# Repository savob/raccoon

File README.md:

# Raccoon

A little raccoon trinket based on an ATtiny and capacitive sensing. The premise is simple, a small circuitboard decorated to be a raccoon on one side has circuitry mounted on the back to illuminate the LED eyes when a touch is detected on the raccoon. Designed to maximize battery life and run of standard coin cells.

My first foray into making PCB art hardwarewise, and both capacitive sensing and really trying to supress power draw with coding.

_All this artwork was drawn by my lovely sister, Dorotea Bajic. Check out their website [dorotea.ca](https://dorotea.ca/), it's far nicer looking than my own._

# Code

The code is pretty simple for the first two revisions given the scope of the projects, and a minor hack was used to get revision 1.0 working. I used the Arduino framework for the first revision but have since moved to using Microchip's own MPLAB to make full use of the chips.

# Hardware

The electrical design of the system is simple, a microcontroller powered directly from a coin cell battery that is connected to a couple LEDs, a capacitance detection pad, and a select few passive components. The challenge with the board for this was the artwork and making it look nice.

Initially an ATtiny85 was selected but later I switched to the tinyAVR 1-series due to dedicated capacitive sensing hardware and reduced power consumption.

# Software Used

KiCad is used to design the hardware, version 9 as of writing.

Arduino IDE 1.8.13 was used to program revision 1.0. MPLAB for revisions 2.0 onwards.

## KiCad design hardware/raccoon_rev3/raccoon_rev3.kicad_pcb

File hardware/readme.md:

# Raccoon Hardware Files

The folders `raccoon_revX` are the actual KiCad projects, `raccoon-art` is the collection of footprints for the artwork derived from the images in the [media](../media/) folder.

# Revision 1.0

These design files are the lightly adjusted version of the original raccoon hardware, to address the hardware bugs related to the programming interface.

# Revision 2.0

A continuation of the work done for the files shared as "Revision 1". Changes from the previous revision:

- Complete removal of the ATtiny85 in favour of the ATtiny1617 _which is definitely overkill for this task but what I had on hand._
- Moved to using a TagConnect programming header to simplify programming. _This does slightly affect the art on the front._
- Added a jumper to cut for current measurement

# Revision 3.0

Tweaking the design of revision 2.0. Changes from the previous revision:

- Changed the main microcontroller to a 1616 since we don't need many GPIO, but I want flash space to try different eye effects, maybe even changing with each touch
- Removed unnecessary passives; the sense resistor, VREF capacitor, secondary decoupling capacitor (100n)
- Split the LED lines for individual eye control, via PWM
- Moved the programming pads to be closer to the edge so some alignment pins align to the PCB outline instead of needing holes in the PCB
- Moved the LED current limiting resistors to be closer to the microcontroller and out of the path of the coin cell
- Added a keepout zone for pour near the current measurement jumper to avoid cutting and then shorting VCC to GND

# Software Used

KiCad version 9 was used for all project files.

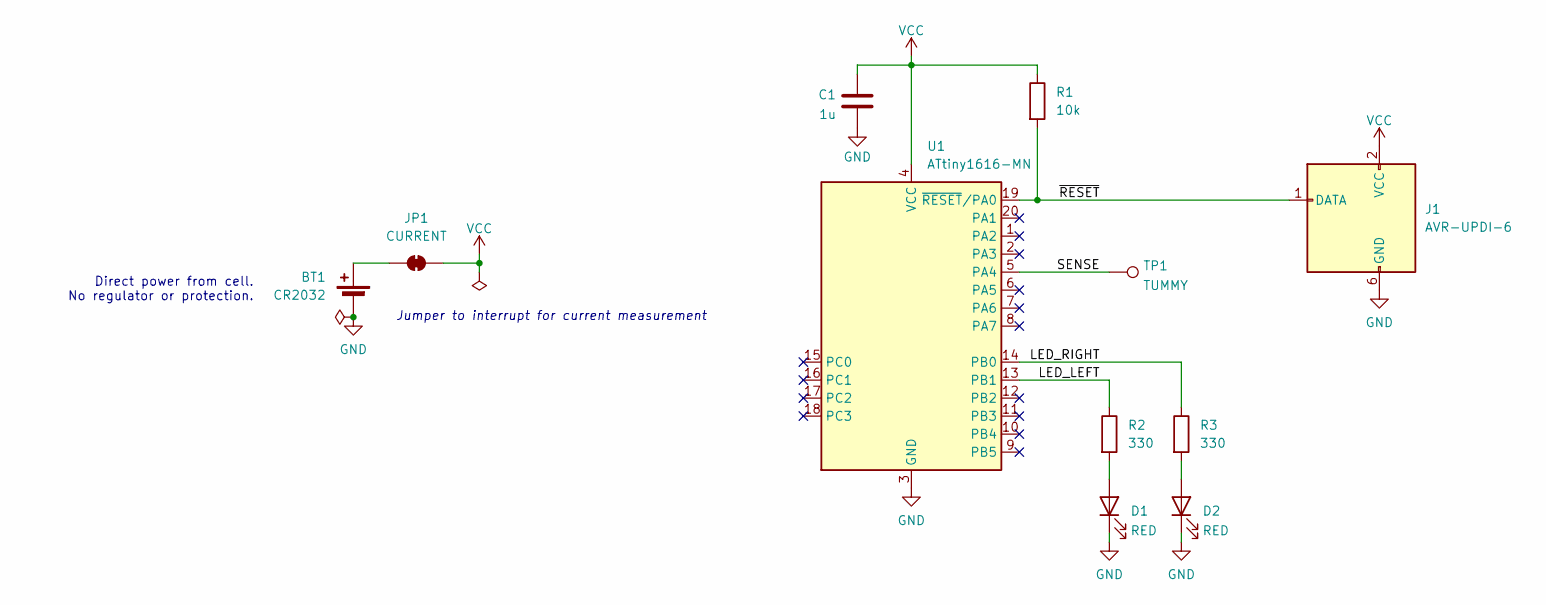
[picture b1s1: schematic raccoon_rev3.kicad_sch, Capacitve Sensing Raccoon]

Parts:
BT1: CR2032; BatteryHolder_Multicomp_BC-2001_1x2032; Manufacturer PN MY-2032-05; LCSC C964830
C1: 1u; C_0603_1608Metric; Manufacturer PN CL10A105KB8NNNC; LCSC C15849
D1, D2: RED; D_0805_2012Metric; Manufacturer PN LTST-C170KRKT; LCSC C94868
J1: AVR-UPDI-6; Tag-Connect_TC2030-IDC-NL_2x03_P1.27mm_Vertical
JP1: CURRENT; SolderJumper-2_P1.3mm_Bridged2Bar_Pad1.0x1.5mm
R1: 10k; R_0603_1608Metric; Manufacturer PN 0603WAF1002T5E; LCSC C25804
R2, R3: 330; R_0603_1608Metric; Manufacturer PN 0603WAF3300T5E; LCSC C23138
TP1: TUMMY; tummy
U1: ATtiny1616-MN; VQFN-20-1EP_3x3mm_P0.4mm_EP1.7x1.7mm; Manufacturer PN ATTINY1616-MNR; LCSC C507118

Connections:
/LED_LEFT: R2.1, U1.13 (PB1)
/LED_RIGHT: R3.1, U1.14 (PB0)
/SENSE: TP1.1, U1.5 (PA4)
/~RESET: J1.1 (DATA), R1.2, U1.19 (~RESET/PA0)
GND: BT1.2 (-), C1.2, D1.1 (K), D2.1 (K), J1.6 (GND), U1.3 (GND), U1.21 (GND)
unnamed: BT1.1 (+), JP1.1 (A)
unnamed: D1.2 (A), R2.2
unnamed: D2.2 (A), R3.2
VCC: C1.1, J1.2 (VCC), JP1.2 (B), R1.1, U1.4 (VCC)

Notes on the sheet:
Jumper to interrupt for current measurement
Direct power from cell. No regulator or protection.

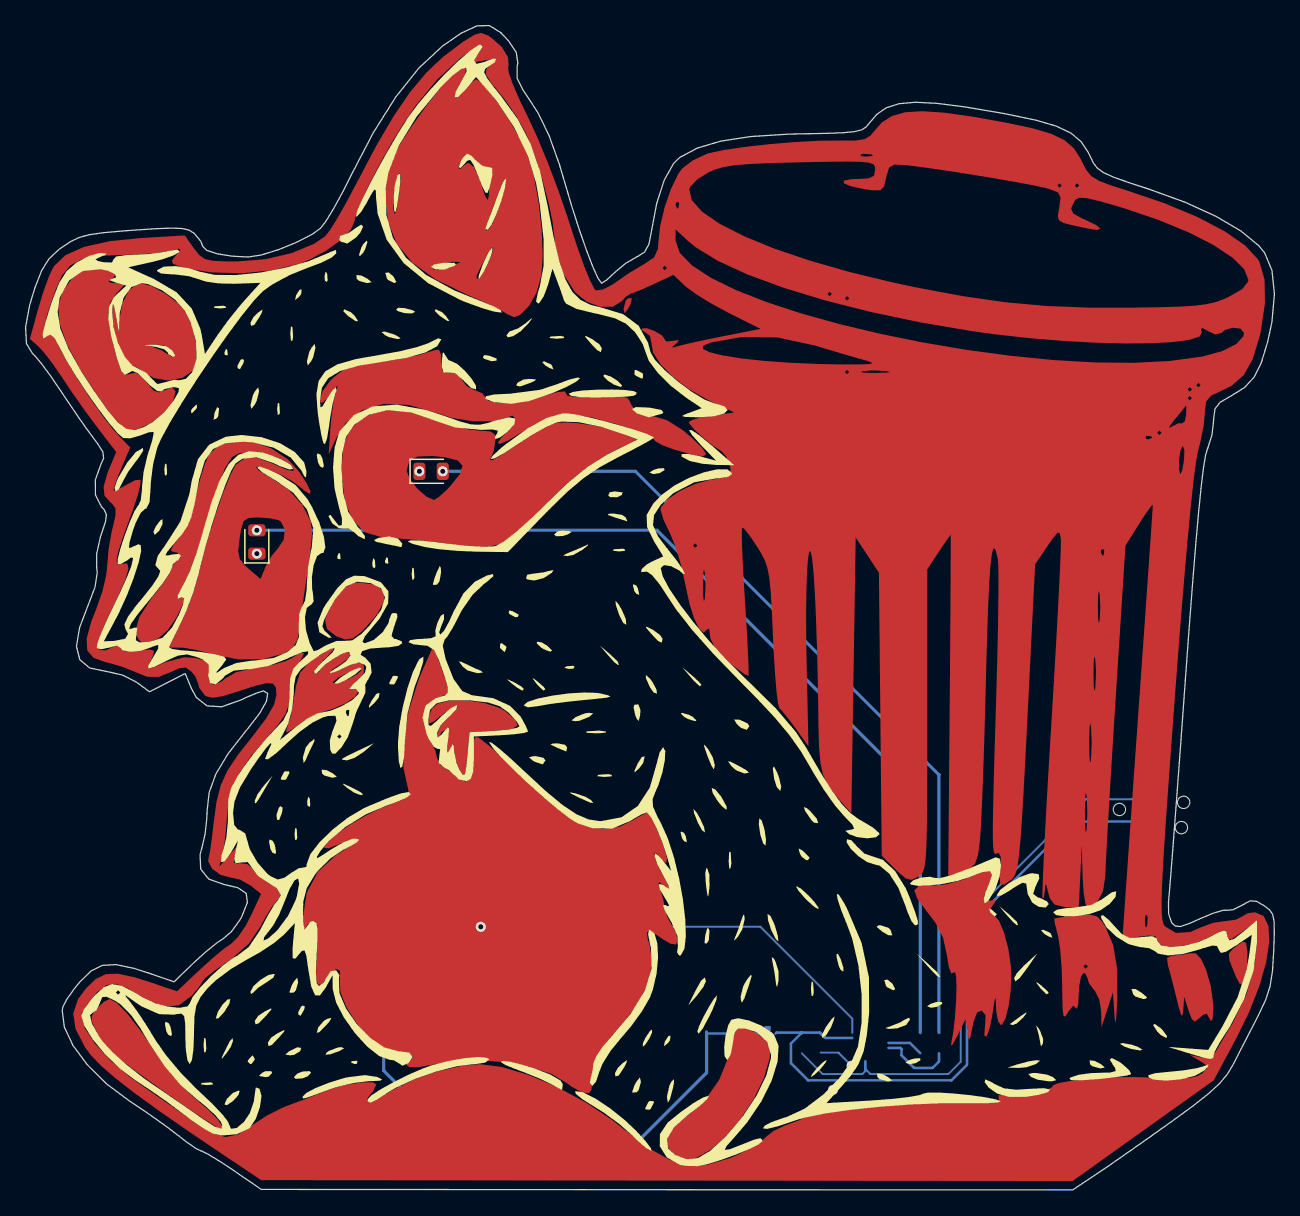
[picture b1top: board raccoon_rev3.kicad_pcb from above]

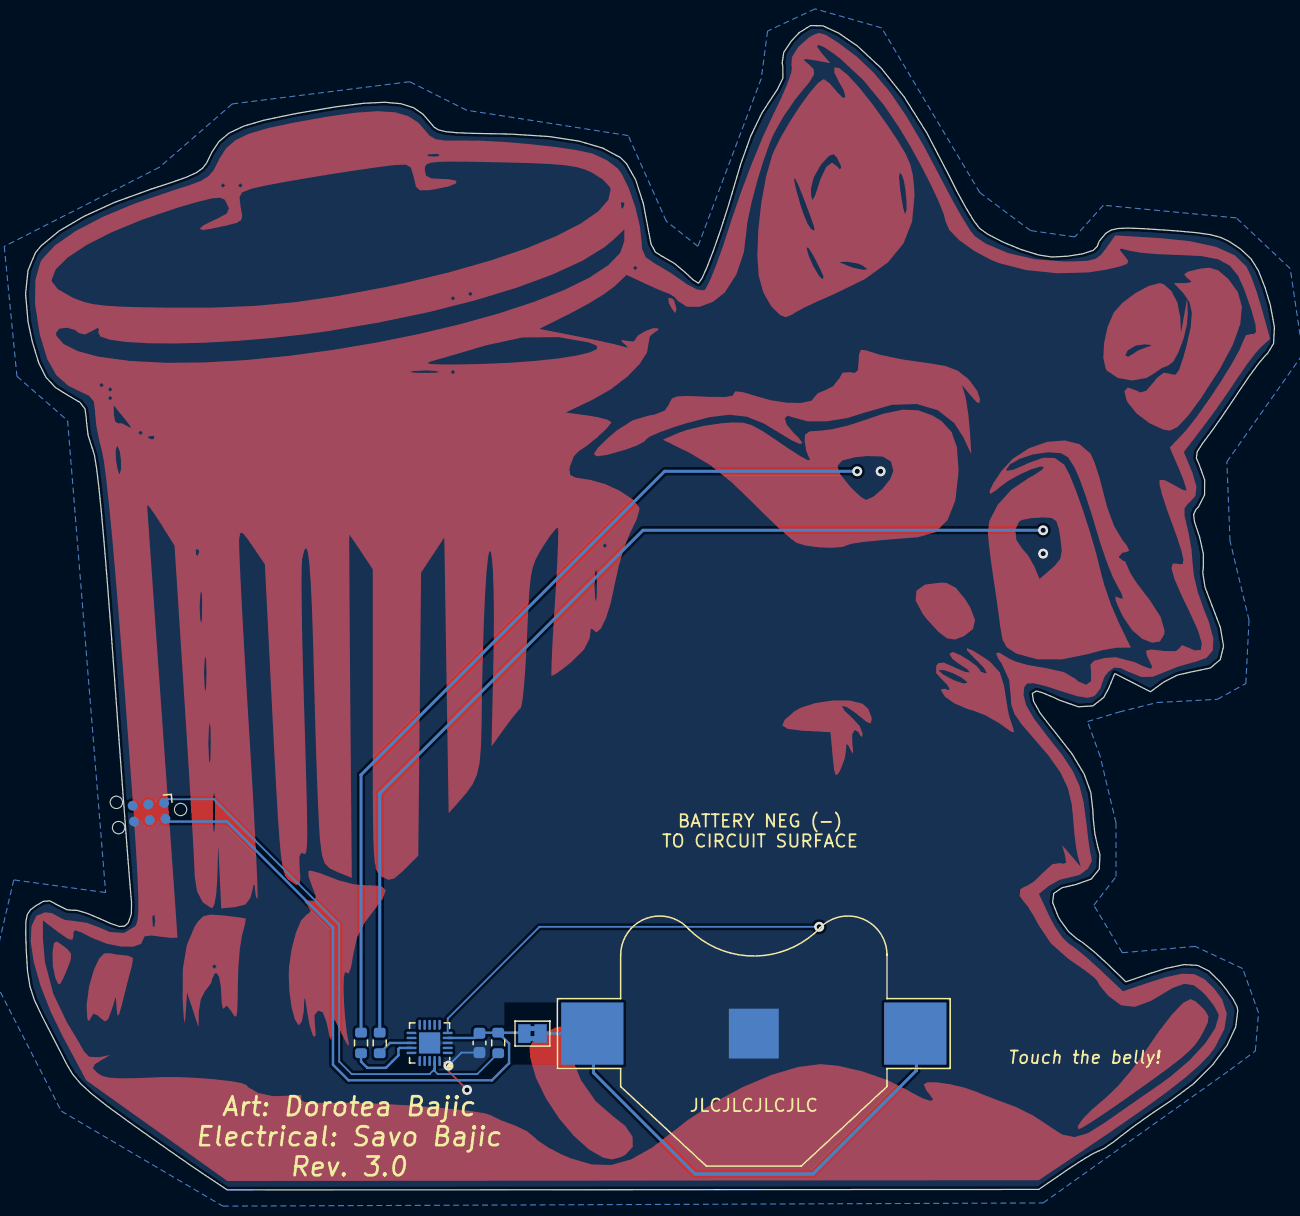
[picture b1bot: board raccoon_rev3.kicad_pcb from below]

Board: 2 copper layers, 100.2 x 93.4 mm, 11 parts (8 on the bottom side), 9 nets.

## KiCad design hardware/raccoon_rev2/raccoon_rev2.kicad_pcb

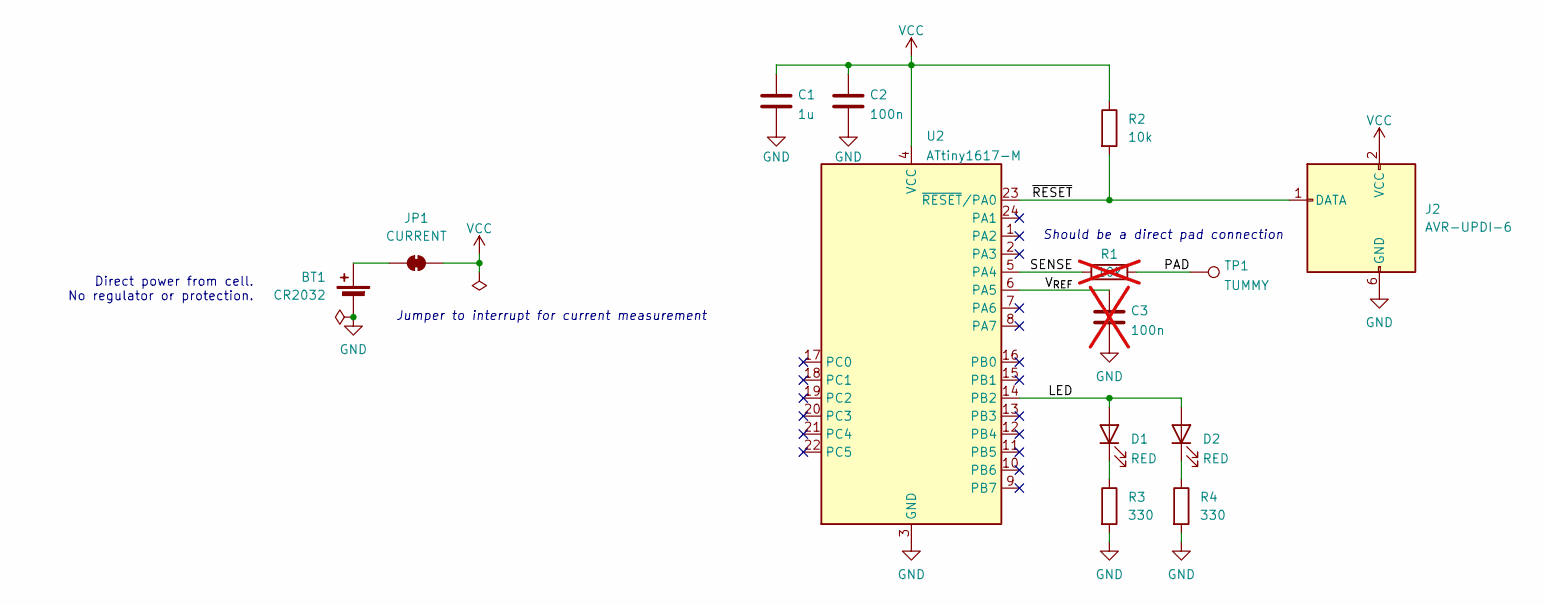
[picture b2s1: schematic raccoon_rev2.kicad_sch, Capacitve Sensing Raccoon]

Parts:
BT1: CR2032; BatteryHolder_Multicomp_BC-2001_1x2032; Manufacturer PN MY-2032-05; LCSC C964830
C1: 1u; C_0603_1608Metric; Manufacturer PN CL10A105KB8NNNC; LCSC C15849
C2: 100n; C_0603_1608Metric; Manufacturer PN CC0603KRX7R9BB104; LCSC C14663
C3: 100n; C_0603_1608Metric; Manufacturer PN CC0603KRX7R9BB104; LCSC C14663; not fitted
D1, D2: RED; D_0805_2012Metric; Manufacturer PN LTST-C170KRKT; LCSC C94868
J2: AVR-UPDI-6; Tag-Connect_TC2030-IDC-NL_2x03_P1.27mm_Vertical
JP1: CURRENT; SolderJumper-2_P1.3mm_Bridged2Bar_Pad1.0x1.5mm
R1: 10k; R_0603_1608Metric; Manufacturer PN 0603WAF1002T5E; LCSC C25804; not fitted
R2: 10k; R_0603_1608Metric; Manufacturer PN 0603WAF1002T5E; LCSC C25804
R3, R4: 330; R_0603_1608Metric; Manufacturer PN 0603WAF3300T5E; LCSC C23138
TP1: TUMMY; tummy
U2: ATtiny1617-M; QFN-24-1EP_4x4mm_P0.5mm_EP2.6x2.6mm; Manufacturer PN ATTINY1617-MNR; LCSC C614176

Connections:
/LED: D1.2 (A), D2.2 (A), U2.14 (PB2)
/PAD: R1.2, TP1.1
/SENSE: R1.1, U2.5 (PA4)
/V_{REF}: C3.1, U2.6 (PA5)
/~RESET: J2.1 (DATA), R2.2, U2.23 (~RESET/PA0)
GND: BT1.2 (-), C1.2, C2.2, C3.2, J2.6 (GND), R3.2, R4.2, U2.3 (GND), U2.25 (GND)
unnamed: BT1.1 (+), JP1.1 (A)
unnamed: D1.1 (K), R3.1
unnamed: D2.1 (K), R4.1
VCC: C1.1, C2.1, J2.2 (VCC), JP1.2 (B), R2.1, U2.4 (VCC)

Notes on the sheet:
Should be a direct pad connection
Jumper to interrupt for current measurement
Direct power from cell. No regulator or protection.

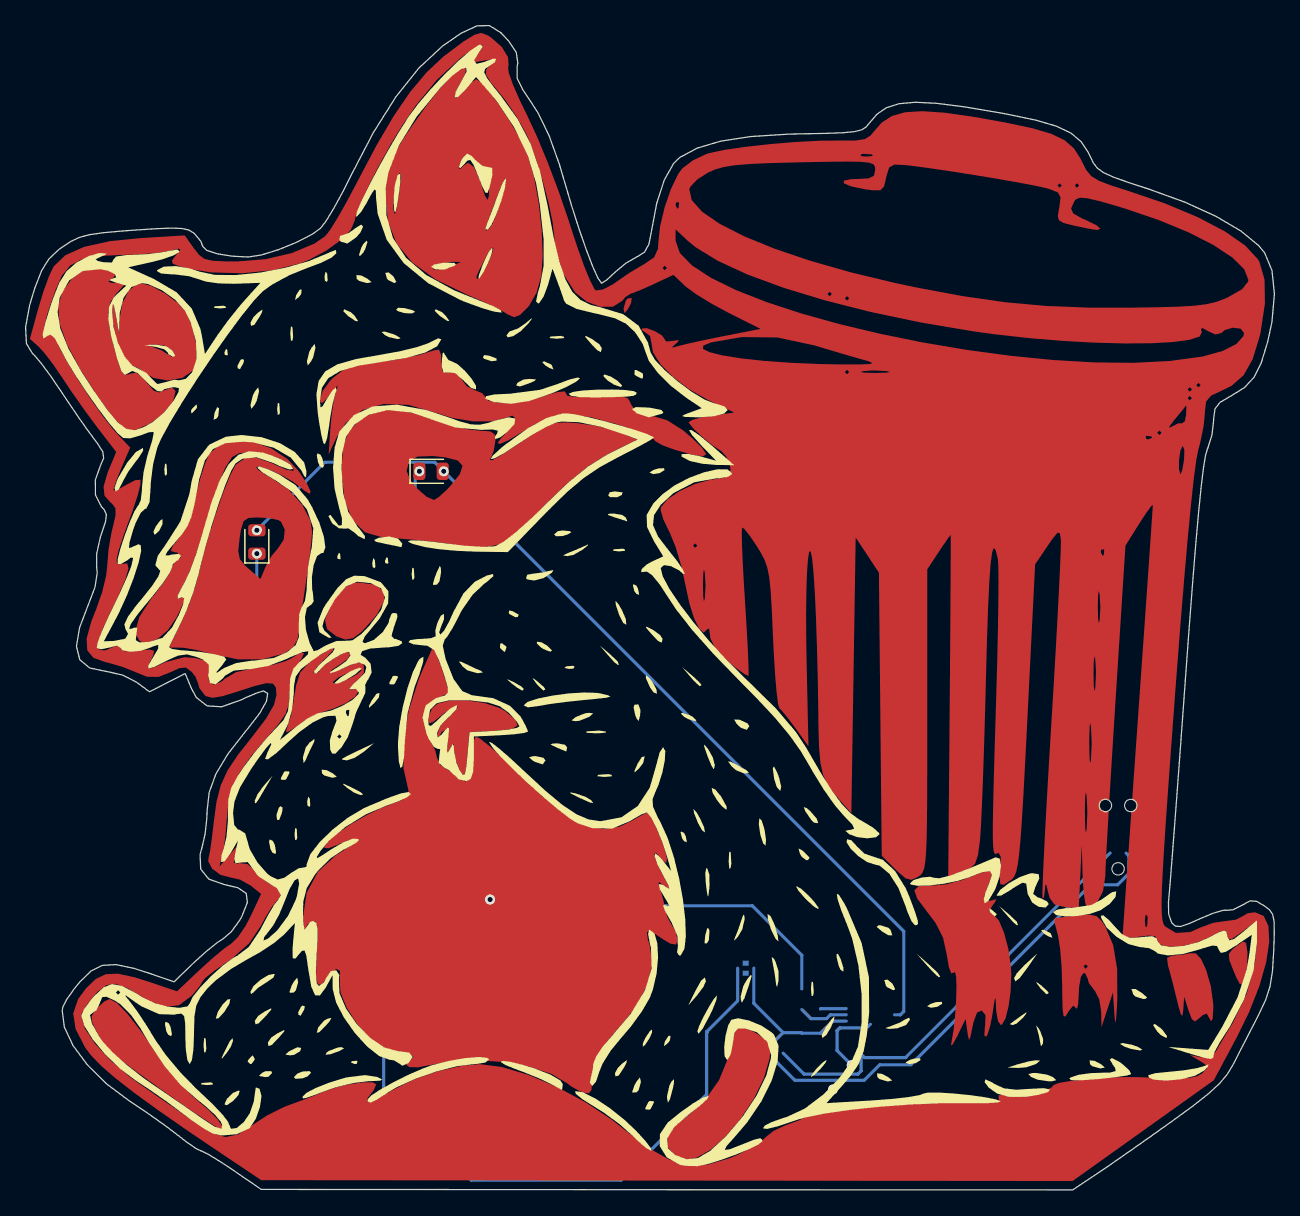
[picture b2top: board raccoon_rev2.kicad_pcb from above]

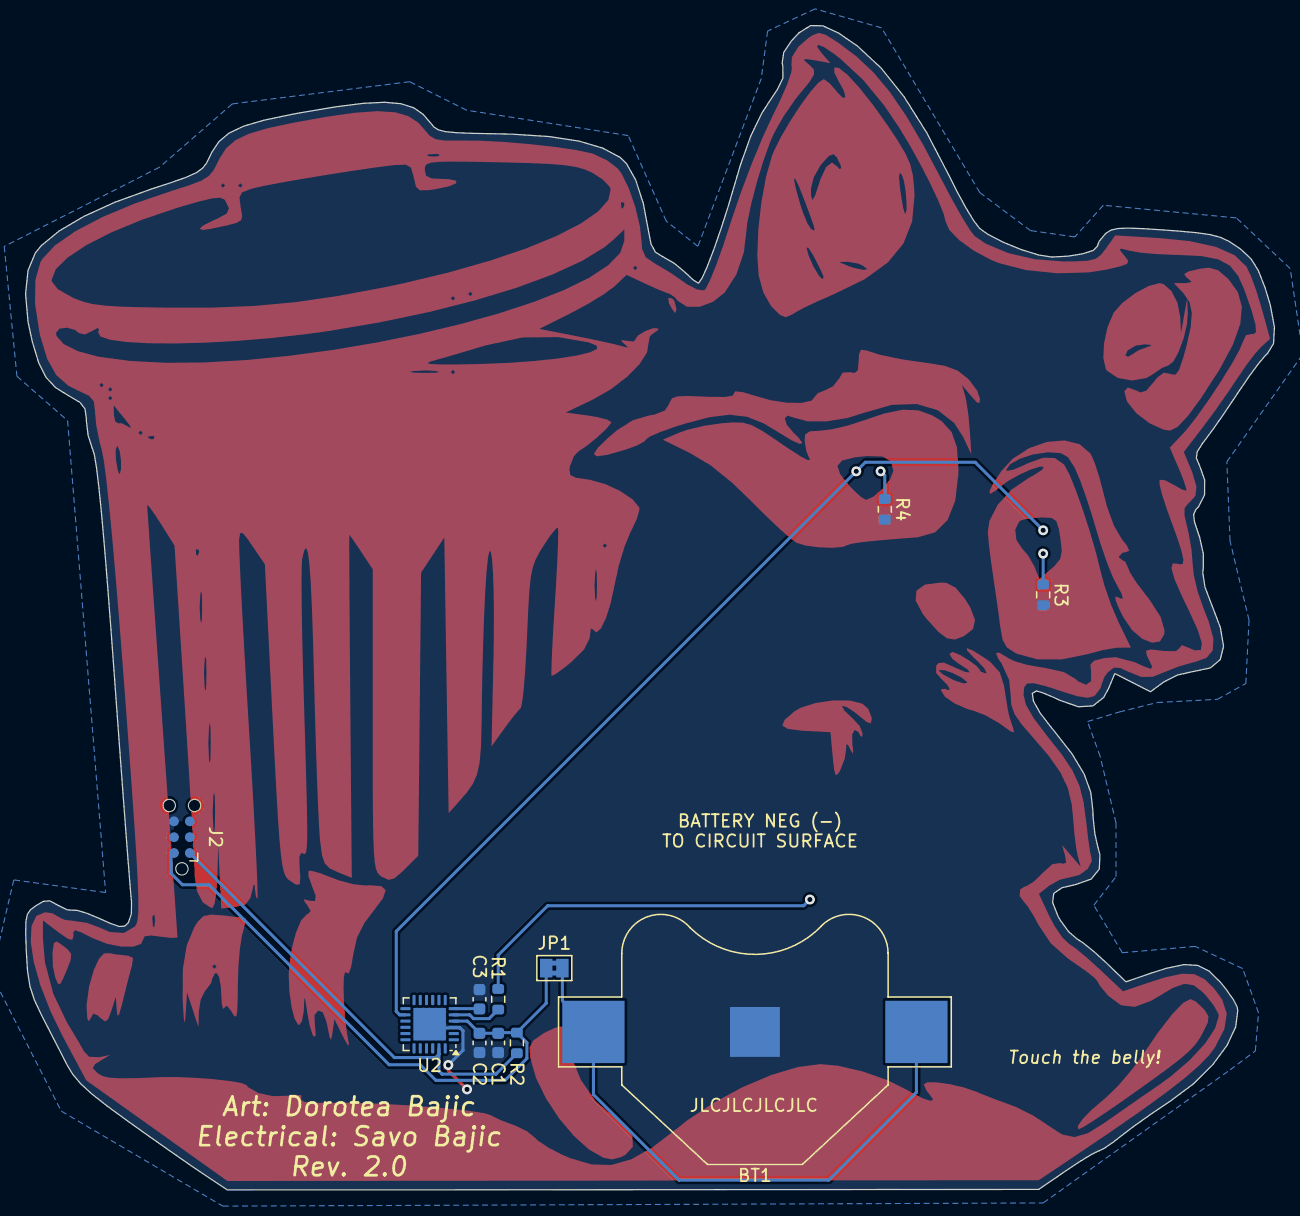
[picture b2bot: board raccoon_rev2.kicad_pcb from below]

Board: 2 copper layers, 100.2 x 93.4 mm, 14 parts (11 on the bottom side), 10 nets.

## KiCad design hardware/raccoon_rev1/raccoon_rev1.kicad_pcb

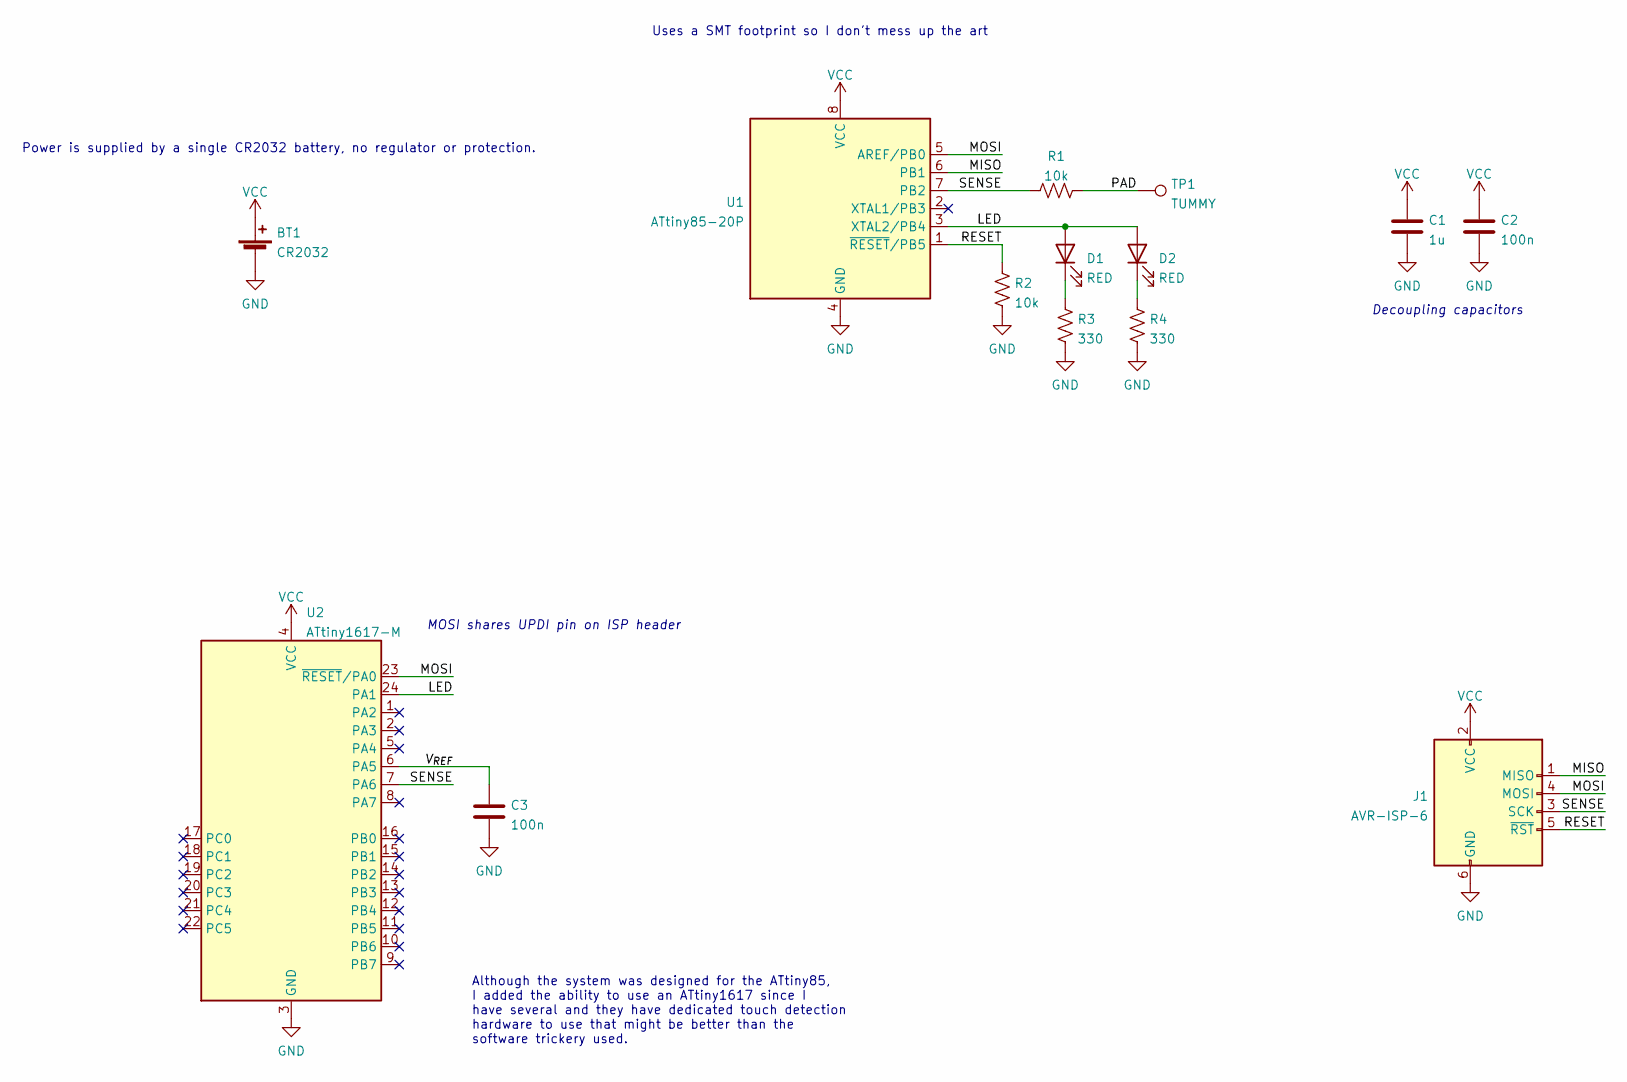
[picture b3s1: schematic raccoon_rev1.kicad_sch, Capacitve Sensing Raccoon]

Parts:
BT1: CR2032; BatteryHolder_Keystone_3002_1x2032
C1: 1u; C_0603_1608Metric
C2, C3: 100n; C_0603_1608Metric
D1, D2: RED; D_0805_2012Metric
J1: AVR-ISP-6; PinHeader_2x03_P2.54mm_Vertical_SMD
R1, R2: 10k; R_0603_1608Metric
R3, R4: 330; R_0603_1608Metric
TP1: TUMMY; tummy
U1: ATtiny85-20P; DIP-8_W7.62mm_SMDSocket_SmallPads
U2: ATtiny1617-M; QFN-24-1EP_4x4mm_P0.5mm_EP2.6x2.6mm

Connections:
/LED: D1.2 (A), D2.2 (A), U1.3 (XTAL2/PB4), U2.24 (PA1)
/MISO: J1.1 (MISO), U1.6 (PB1)
/MOSI: J1.4 (MOSI), U1.5 (AREF/PB0), U2.23 (~RESET/PA0)
/PAD: R1.2, TP1.1
/RESET: J1.5 (~RST), R2.1, U1.1 (~RESET/PB5)
/SENSE: J1.3 (SCK), R1.1, U1.7 (PB2), U2.7 (PA6)
/V_{REF}: C3.1, U2.6 (PA5)
GND: BT1.2 (-), C1.2, C2.2, C3.2, J1.6 (GND), R2.2, R3.2, R4.2, U1.4 (GND), U2.3 (GND), U2.25 (GND)
unnamed: D1.1 (K), R3.1
unnamed: D2.1 (K), R4.1
VCC: BT1.1 (+), C1.1, C2.1, J1.2 (VCC), U1.8 (VCC), U2.4 (VCC)

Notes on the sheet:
Although the system was designed for the ATtiny85, I added the ability to use an ATtiny1617 since I have several and they have dedicated touch detection hardware to use that might be better than the software trickery used.
MOSI shares UPDI pin on ISP header
Decoupling capacitors
Power is supplied by a single CR2032 battery, no regulator or protection.
Uses a SMT footprint so I don't mess up the art

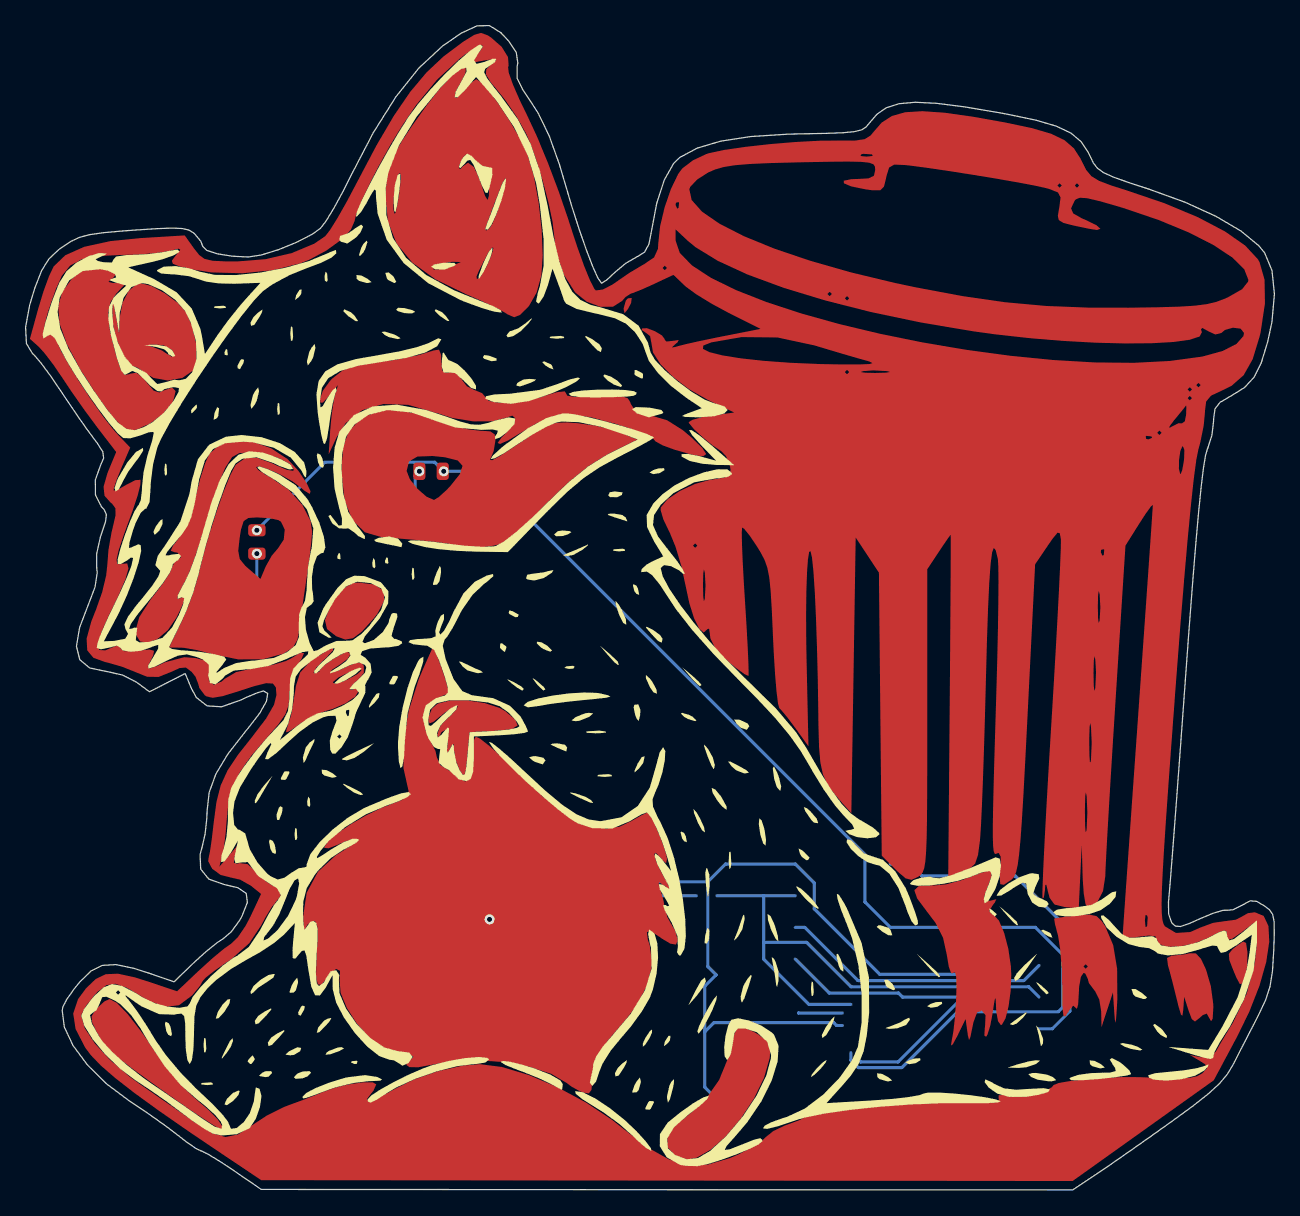
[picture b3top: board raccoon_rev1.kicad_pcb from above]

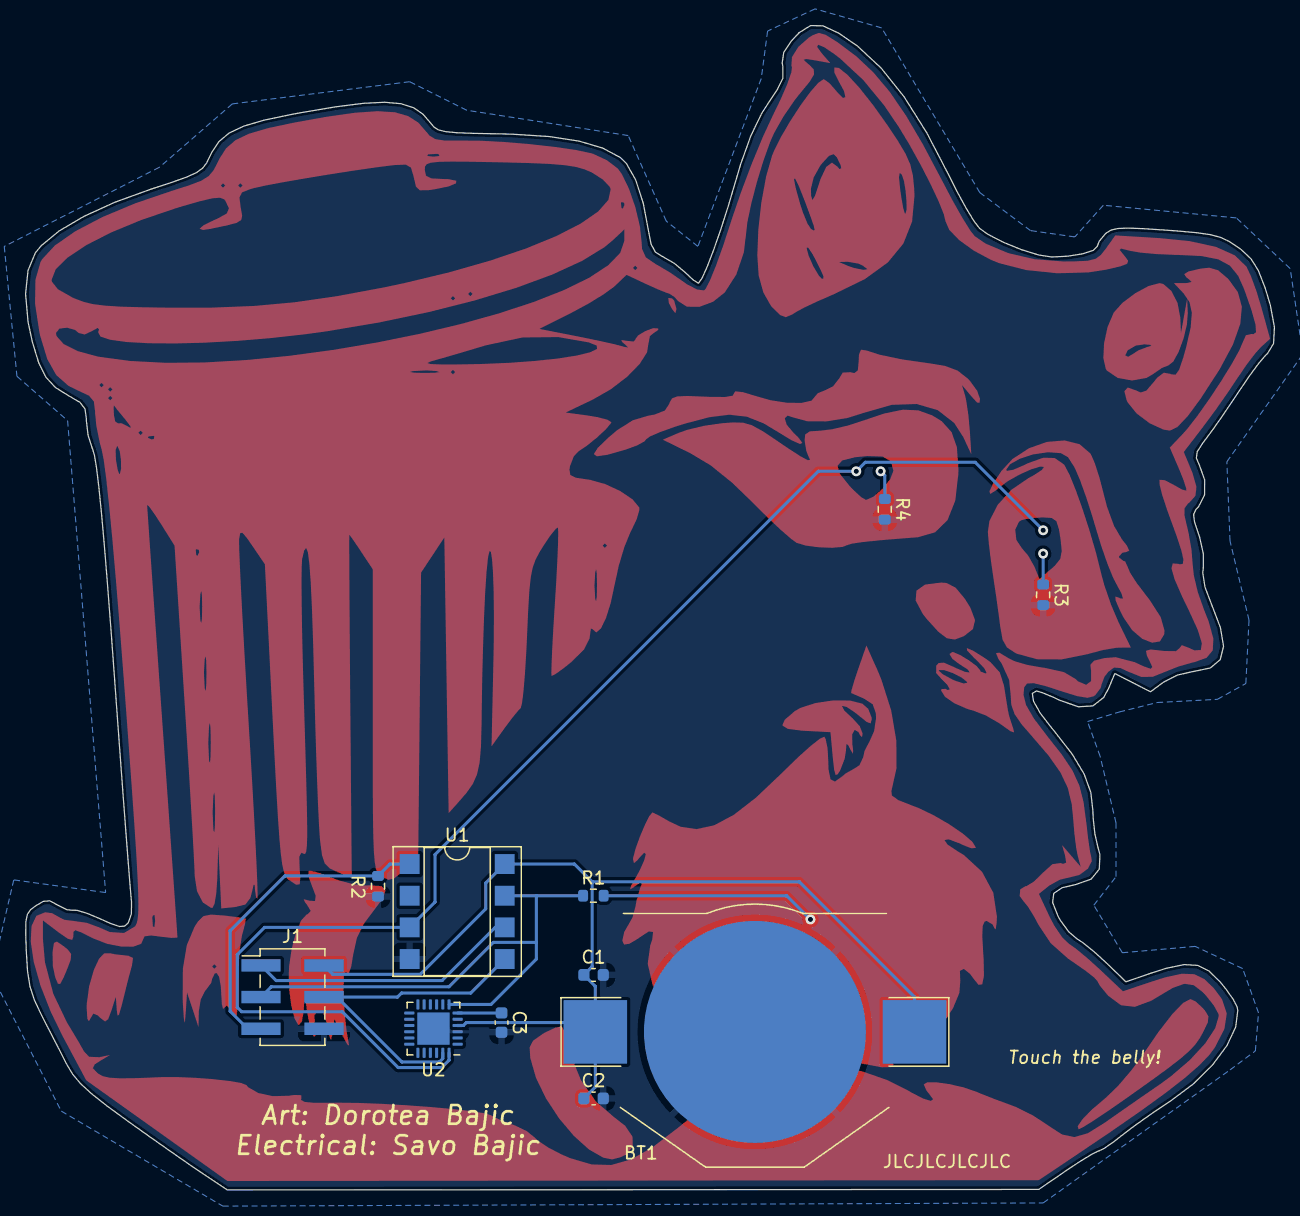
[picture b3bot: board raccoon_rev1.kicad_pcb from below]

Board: 2 copper layers, 100.2 x 93.4 mm, 14 parts (11 on the bottom side), 11 nets.

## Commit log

2021-12-11 Initial upload of code
2021-12-11 Preliminary readme
2022-03-07 Updated code to boards
    Reflected some changes needed on the boards, namely pin allocations for capacitance sensing and increased the frequency of touch checks. Some formatting was updated too.
2022-03-07 Updated readme
    Filled in the links for what I used.
2022-03-08 Updated firmware based on testing
    Updated firmware with the results of my tests, such as tuning as well as some readability improvements.
2022-03-08 Update bias more often if "held"
    Since the raccoon only checks every other second, if it is unlikely to be held for more than 10 checks (20 seconds) so have it update the bias then if needed.
2022-03-21 Uploaded hardware files
    The hardware files uploaded are the revised version. They fix the programming header issue I had (but not the "sense" connection). I included a zip with the "original" version I had manufactured.
2024-01-04 Reorganization
2024-01-04 Added `.gitignore`
2024-01-04 Updating project to KiCad 7
2024-01-04 Added licence
2025-08-03 Hardware revision 2.0
2025-08-03 Removed lock file
2025-09-02 Added alternate PN as ordered
2025-10-21 Minor hardware assembly changes
2025-10-21 Upload of firmware for rev 2.0
2025-10-22 Touching up compiler options
2025-10-23 Updated components being placed
2025-10-25 Added designs and preliminary hardware for revision 3.0
2025-10-25 Added Dorotea shout outs
2025-10-25 Updated readmes related to firmware
